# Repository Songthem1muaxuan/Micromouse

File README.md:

# Micromouse
Just a small project that I made for fun
# Hardware:
- 1 STM32F103C8Tx
- 1 Motor driver TB6612FNG
- 2 N20 encoder motors (220RPM)
- 1 MPU 6050
- 4 IR sensors
- 1 Silergy SY8303AIC (or you can use MP2303, MP2307DN ur choice :> )

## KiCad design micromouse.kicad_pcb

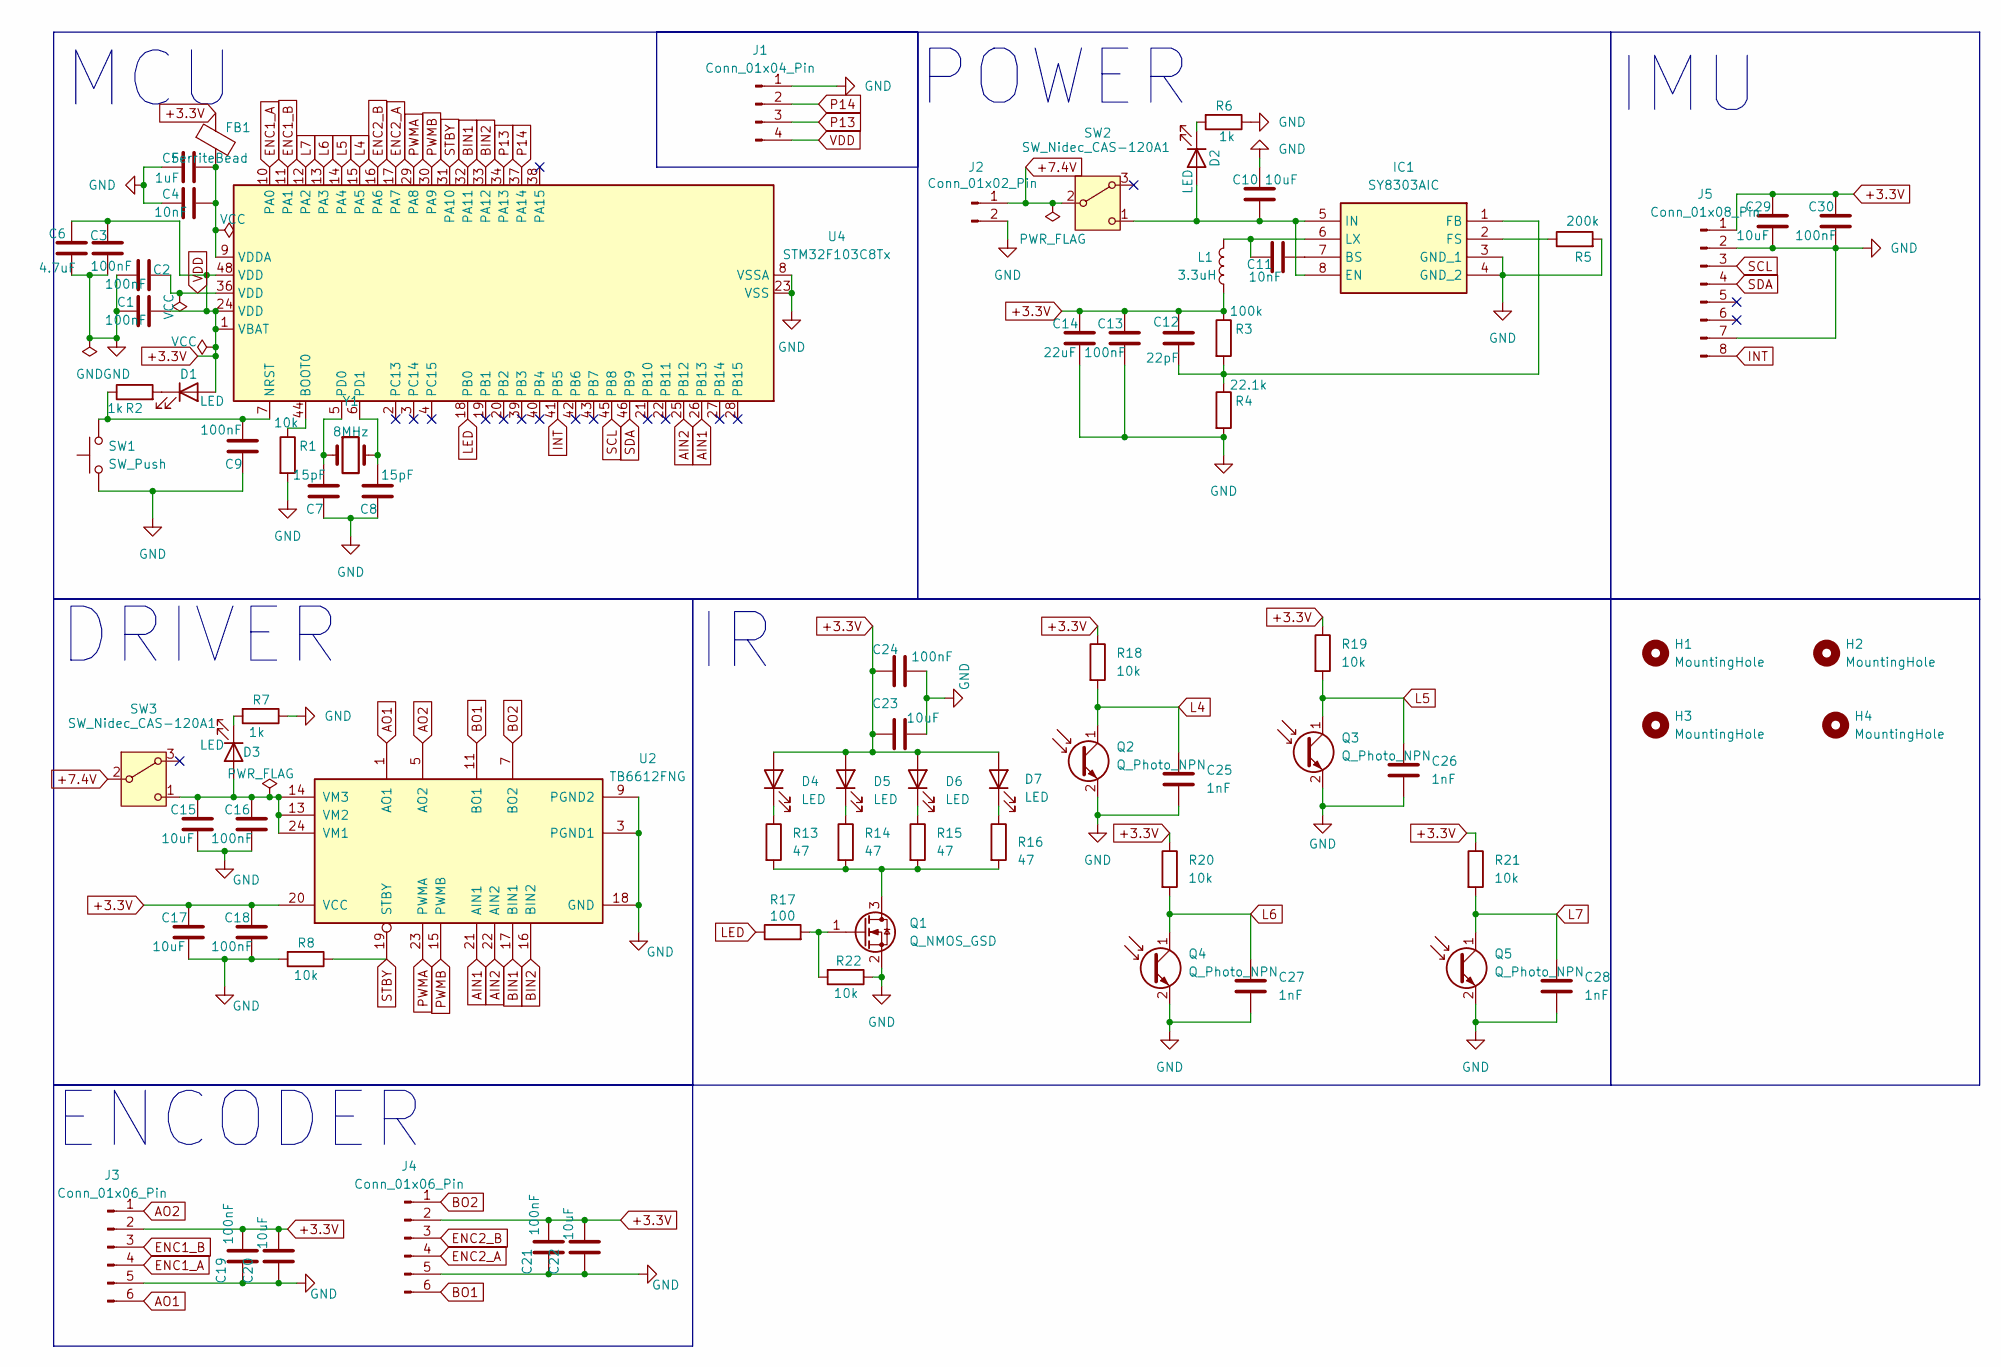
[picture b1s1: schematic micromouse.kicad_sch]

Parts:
C1, C2, C3, C9, C13, C16, C18, C19, C21, C24, C30: 100nF; C_0603_1608Metric_Pad1.08x0.95mm_HandSolder
C4, C11: 10nF; C_0603_1608Metric_Pad1.08x0.95mm_HandSolder
C5: 1uF; C_0805_2012Metric_Pad1.18x1.45mm_HandSolder
C6: 4.7uF; C_0805_2012Metric_Pad1.18x1.45mm_HandSolder
C7, C8: 15pF; C_0603_1608Metric_Pad1.08x0.95mm_HandSolder
C10, C15, C17, C20, C22, C23, C29: 10uF; C_0805_2012Metric_Pad1.18x1.45mm_HandSolder
C12: 22pF; C_0603_1608Metric_Pad1.08x0.95mm_HandSolder
C14: 22uF; C_1206_3216Metric_Pad1.33x1.80mm_HandSolder
C25, C26, C27, C28: 1nF; C_0603_1608Metric_Pad1.08x0.95mm_HandSolder
D1, D2, D3: LED; LED_0805_2012Metric_Pad1.15x1.40mm_HandSolder
D4, D5, D6, D7: LED; LED_D5.0mm_Horizontal_O1.27mm_Z3.0mm_Clear
FB1: FerriteBead; L_0805_2012Metric_Pad1.05x1.20mm_HandSolder
H1, H2, H3, H4: MountingHole; MountingHole_2.2mm_M2
IC1: SY8303AIC; SOT65P280X110-8N; Manufacturer_Part_Number SY8303AIC
J1: Conn_01x04_Pin; PinHeader_1x04_P2.54mm_Vertical
J2: Conn_01x02_Pin; JST_XH_B2B-XH-A_1x02_P2.50mm_Vertical
J3, J4: Conn_01x06_Pin; JST_XH_B6B-XH-A_1x06_P2.50mm_Vertical
J5: Conn_01x08_Pin; PinSocket_1x08_P2.54mm_Vertical
L1: 3.3uH; L_Taiyo-Yuden_NR-40xx_HandSoldering
Q1: Q_NMOS_GSD; SOT-23_Handsoldering
Q2, Q3, Q4, Q5: Q_Photo_NPN; LED_D5.0mm_Horizontal_O1.27mm_Z3.0mm_IRBlack
R1, R8, R18, R19, R20, R21, R22: 10k; R_0603_1608Metric_Pad0.98x0.95mm_HandSolder
R2, R6, R7: 1k; R_0603_1608Metric_Pad0.98x0.95mm_HandSolder
R3: 100k; R_0603_1608Metric_Pad0.98x0.95mm_HandSolder
R4: 22.1k; R_0603_1608Metric_Pad0.98x0.95mm_HandSolder
R5: 200k; R_0603_1608Metric_Pad0.98x0.95mm_HandSolder
R13, R14, R15, R16: 47; R_0805_2012Metric_Pad1.20x1.40mm_HandSolder
R17: 100; R_0603_1608Metric_Pad0.98x0.95mm_HandSolder
SW1: SW_Push; SW_SPST_TS-1088-xR020
SW2, SW3: SW_Nidec_CAS-120A1; SW_Slide-03_Wuerth-WS-SLTV_10x2.5x6.4_P2.54mm
U2: TB6612FNG; SSOP-24_5.3x8.2mm_P0.65mm
U4: STM32F103C8Tx; LQFP-48_7x7mm_P0.5mm
Y1: 8MHz; Crystal_SMD_3215-2Pin_3.2x1.5mm

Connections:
+3.3V: C1.2, C3.2, C6.2, C12.2, C13.2, C14.2, C17.2, C18.2, C19.1, C20.1, C21.1, C22.1, C23.2, C24.2, C29.2, C30.2, D1.2 (A), D4.2 (A), D5.2 (A), D6.2 (A), D7.2 (A), FB1.1, J3.2, J4.2, J5.1, L1.1, R3.1, R18.1, R19.1, R20.1, R21.1, U2.20 (VCC), U4.1 (VBAT), U4.24 (VDD), U4.48 (VDD)
AIN1: U2.21 (AIN1), U4.26 (PB13)
AIN2: U2.22 (AIN2), U4.25 (PB12)
AO1: J3.6, U2.1 (AO1), U2.2 (AO1)
AO2: J3.1, U2.5 (AO2), U2.6 (AO2)
BIN1: U2.17 (BIN1), U4.32 (PA11)
BIN2: U2.16 (BIN2), U4.33 (PA12)
BO1: J4.6, U2.11 (BO1), U2.12 (BO1)
BO2: J4.1, U2.7 (BO2), U2.8 (BO2)
ENC1_A: J3.4, U4.10 (PA0)
ENC1_B: J3.3, U4.11 (PA1)
ENC2_A: J4.4, U4.17 (PA7)
ENC2_B: J4.3, U4.16 (PA6)
GND: C1.1, C2.1, C3.1, C4.1, C5.1, C6.1, C7.1, C8.1, C9.1, C10.2, C13.1, C14.1, C15.1, C16.1, C17.1, C18.1, C19.2, C20.2, C21.2, C22.2, C23.1, C24.1, C25.2, C26.2, C27.2, C28.2, C29.1, C30.1, IC1.3 (GND_1), IC1.4 (GND_2), J1.1, J2.2, J3.5, J4.5, J5.2, J5.7, Q1.2 (S), Q2.2 (E), Q3.2 (E), Q4.2 (E), Q5.2 (E), R1.2, R4.2, R5.2, R6.1, R7.1, R8.2, R22.1, SW1.1, U2.3 (PGND1), U2.4 (PGND1), U2.9 (PGND2), U2.10 (PGND2), U2.18 (GND), U4.8 (VSSA), U4.23 (VSS), U4.35 (VSS), U4.47 (VSS); also elsewhere on the board
INT: J5.8, U4.41 (PB5)
L4: C25.1, Q2.1 (C), R18.2, U4.15 (PA5)
L5: C26.1, Q3.1 (C), R19.2, U4.14 (PA4)
L6: C27.1, Q4.1 (C), R20.2, U4.13 (PA3)
L7: C28.1, Q5.1 (C), R21.2, U4.12 (PA2)
LED: R17.1, U4.18 (PB0)
unnamed: D1.1 (K), R2.2
unnamed 22: C10.1, D2.2 (A), IC1.5 (IN), IC1.8 (EN), SW2.1 (C); also elsewhere on the board
unnamed: D2.1 (K), R6.2
unnamed 24: C15.2, C16.2, D3.2 (A), SW3.1 (C), U2.13 (VM2), U2.14 (VM3), U2.24 (VM1); also elsewhere on the board
unnamed: D3.1 (K), R7.2
unnamed: D4.1 (K), R13.1
unnamed: D5.1 (K), R14.1
unnamed: D6.1 (K), R15.1
unnamed: D7.1 (K), R16.1
unnamed: C11.1, IC1.7 (BS)
unnamed: C12.1, IC1.1 (FB), R3.2, R4.1
unnamed: IC1.2 (FS), R5.1
unnamed: C11.2, IC1.6 (LX), L1.2
unnamed: J2.1, SW2.2 (B), SW3.2 (B)
unnamed: Q1.3 (D), R13.2, R14.2, R15.2, R16.2
unnamed: Q1.1 (G), R17.2, R22.2
unnamed: R1.1, U4.44 (BOOT0)
unnamed 38: C9.2, R2.1, SW1.2, U4.7 (NRST); also elsewhere on the board
unnamed: C7.2, U4.5 (PD0), Y1.1
unnamed: C8.2, U4.6 (PD1), Y1.2
unnamed: C4.2, C5.2, FB1.2, U4.9 (VDDA)
P13: J1.3, U4.34 (PA13); also elsewhere on the board
P14: J1.2, U4.37 (PA14); also elsewhere on the board
PWMA: U2.23 (PWMA), U4.29 (PA8)
PWMB: U2.15 (PWMB), U4.30 (PA9)
SCL: J5.3, U4.45 (PB8)
SDA: J5.4, U4.46 (PB9)
STBY: R8.1, U2.19 (STBY), U4.31 (PA10)
VDD: C2.2, J1.4, U4.36 (VDD); also elsewhere on the board

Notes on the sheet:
DRIVER
POWER
IMU
ENCODER
MCU

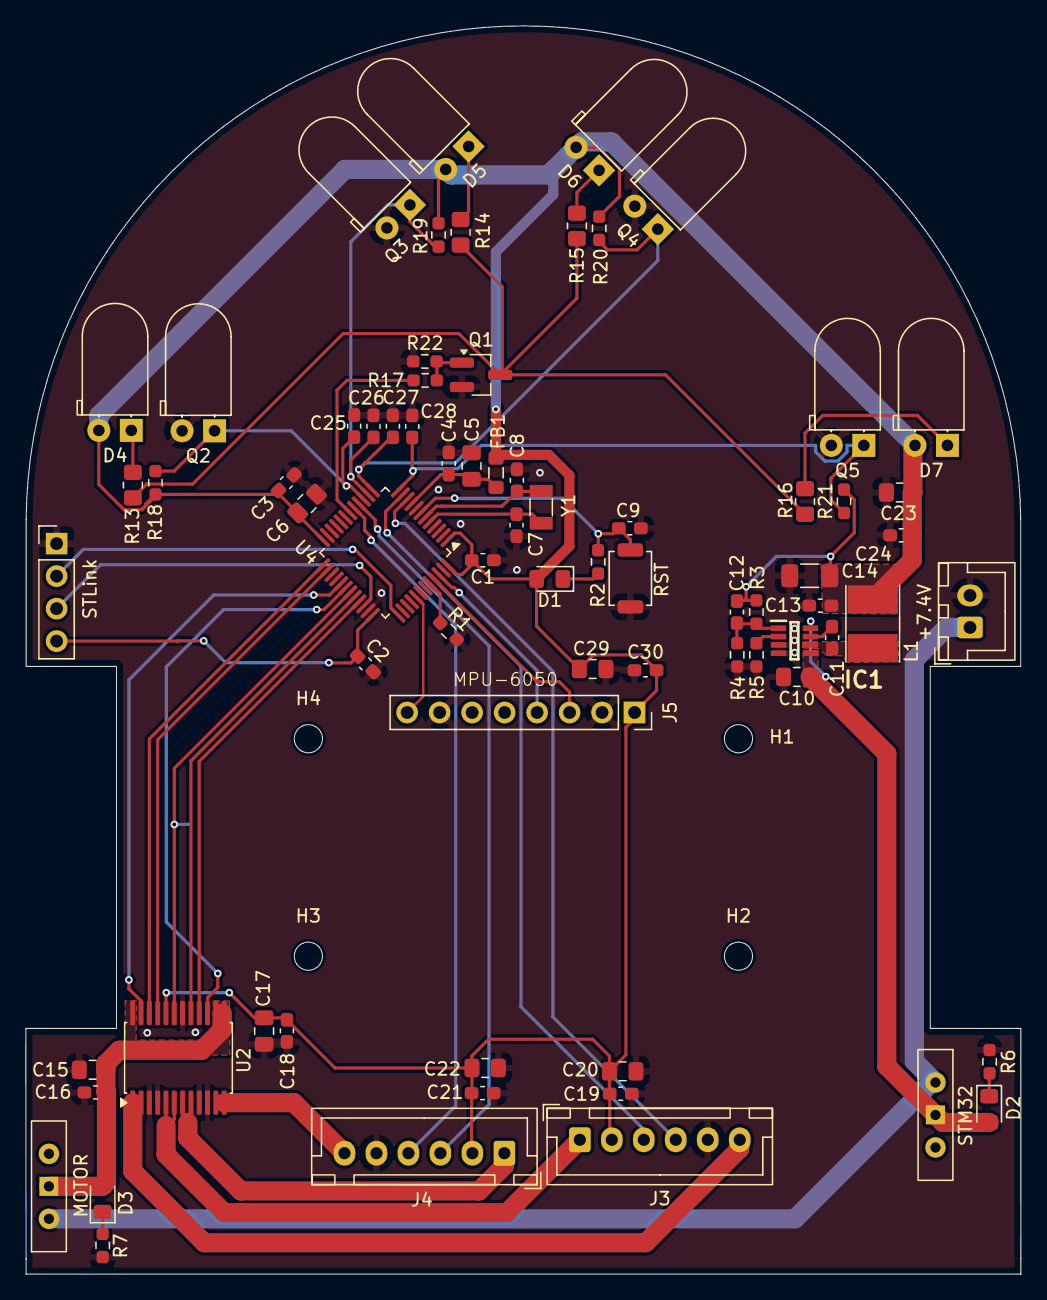
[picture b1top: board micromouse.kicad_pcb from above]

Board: 2 copper layers, 77.8 x 97.6 mm, 78 parts (1 on the bottom side), 49 nets.

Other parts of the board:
+7.4V: Conn_01x02_Pin; JST_XH_B2B-XH-A_1x02_P2.50mm_Vertical
MOTOR: SW_Nidec_CAS-120A1; SW_Slide-03_Wuerth-WS-SLTV_10x2.5x6.4_P2.54mm
RST: SW_Push; SW_SPST_TS-1088-xR020
STLink: Conn_01x04_Pin; PinHeader_1x04_P2.54mm_Vertical
STM32: SW_Nidec_CAS-120A1; SW_Slide-03_Wuerth-WS-SLTV_10x2.5x6.4_P2.54mm

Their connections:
+7.4V: +7.4V.1, MOTOR.2 (B), STM32.2 (B)
GND: +7.4V.2, RST.1, STLink.1; also elsewhere on the board
unnamed 22: STM32.1 (C); also elsewhere on the board
unnamed 24: MOTOR.1 (C); also elsewhere on the board
unnamed 38: RST.2; also elsewhere on the board
P13: STLink.3; also elsewhere on the board
P14: STLink.2; also elsewhere on the board
VDD: STLink.4; also elsewhere on the board
